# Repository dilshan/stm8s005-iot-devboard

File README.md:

# STM8S005C6T6 Ethernet development board

This is an Ethernet development board based on [STM8S005C6T6](https://www.st.com/resource/en/datasheet/stm8s005c6.pdf), designed specifically for IoT related applications. This development board consists of [ENC28J60](http://ww1.microchip.com/downloads/en/devicedoc/39662c.pdf), 10BASE-T stand-alone Ethernet controller, [CH340G](https://cdn.sparkfun.com/datasheets/Dev/Arduino/Other/CH340DS1.PDF), USB serial interface, 2 LED indicators, and passive buzzer unit.

The firmware framework for this development board has been developed using [SDCC](http://sdcc.sourceforge.net/). To enable IPv4 support, we convert the [EtherCard](https://github.com/njh/EtherCard) driver, which is available for the *Arduino* platform. The current version of this driver supports all other *EtherCard* functions except TCP support.

In the given design, the SPI terminals of the MCU are connected to the ENC28J60 Ethernet controller. All SPI terminals, such as *MISO* / *PC7*, *MOSI* / *PC6*, and *SCK* / *PC5*, are connected directly to the Ethernet controller. In addition, the *PC4* terminal of the MCU is used as ENC28J60, *CHIP-SELECT*. 

The CH340G USB serial interface is connected to the *UART2* terminals of the MCU. In STM8S005C6T6, the *UART2* is mapped to the *PD6* and *PD5* terminals of the MCU. The USB interface of this development board consists of the jack-sense feature. The jack-sense status can access from *PD7*.

The minor peripherals such as LED indicators and buzzer are connected to the *PORTD* of the MCU. The LED indicators are connected to terminals *PD0* and *PD1* and can be activated or deactivated via jumpers. The passive buzzer is connected to *PD4* and can run through the STM8 beep sound generator unit.

All peripherals of this development board are powered by a 3.3V supply. The recommended supply voltage for this development board is  5V to 9V.

In addition to the STM8S005C6T6, this development board supports the following STM8 series, LQFP48 packaged microcontrollers: [STM8S007C8T6](https://www.st.com/resource/en/datasheet/stm8s007c8.pdf), [STM8S207C8T6](https://www.st.com/resource/en/datasheet/stm8s207c8.pdf), and [STM8S105C6T6](https://www.st.com/resource/en/datasheet/stm8s105c6.pdf).

The schematic and PCB design of this project is released under the terms of [CERN-OHL-W Version 2.0](https://ohwr.org/cern_ohl_w_v2.pdf). The firmware framework is released under the terms of the [GNU GPL 2.0](https://github.com/dilshan/stm8s005-iot-devboard/blob/main/LICENSE) license.

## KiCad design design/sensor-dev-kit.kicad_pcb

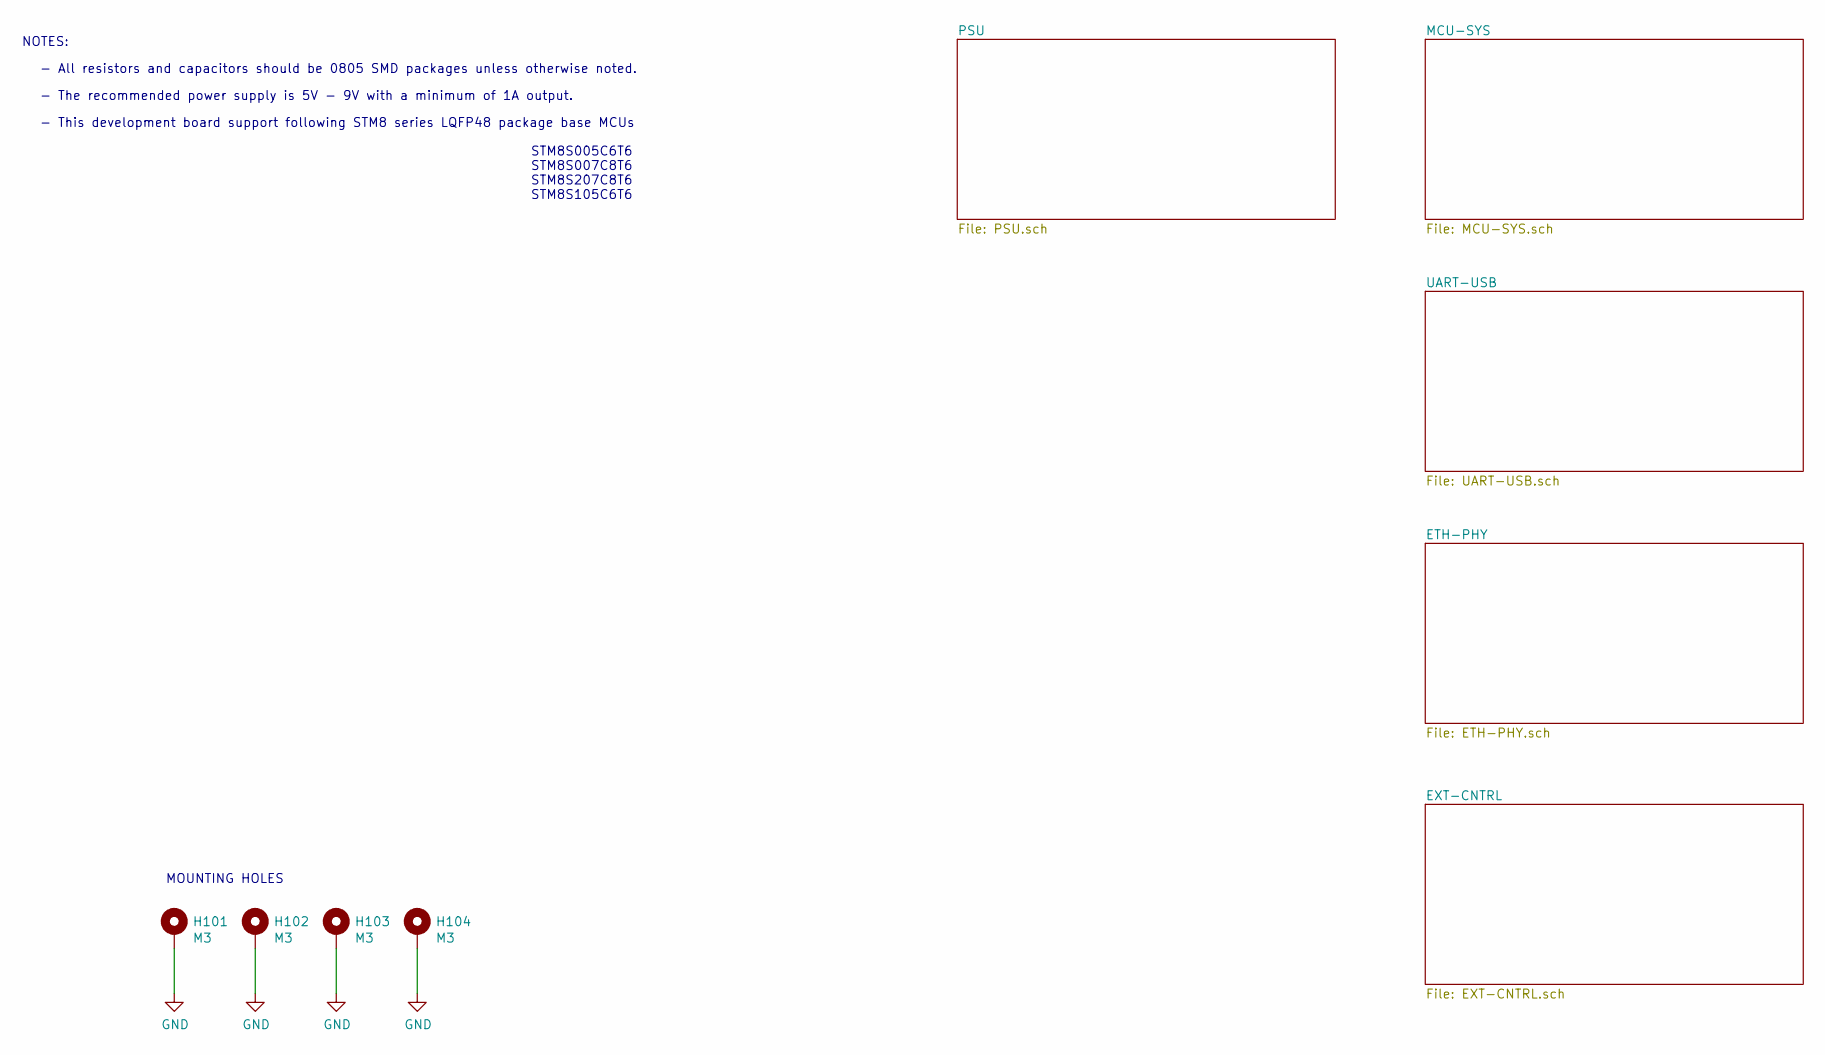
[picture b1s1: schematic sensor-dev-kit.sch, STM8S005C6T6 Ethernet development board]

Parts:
H101, H102, H103, H104: M3; MountingHole_3.2mm_M3_Pad_Via

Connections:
GND: H101.1, H102.1, H103.1, H104.1; also elsewhere on the board

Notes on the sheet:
NOTES:
- All resistors and capacitors should be 0805 SMD packages unless otherwise noted.
- The recommended power supply is 5V - 9V with a minimum of 1A output.
STM8S005C6T6 STM8S007C8T6 STM8S207C8T6 STM8S105C6T6
- This development board support following STM8 series LQFP48 package base MCUs
MOUNTING HOLES

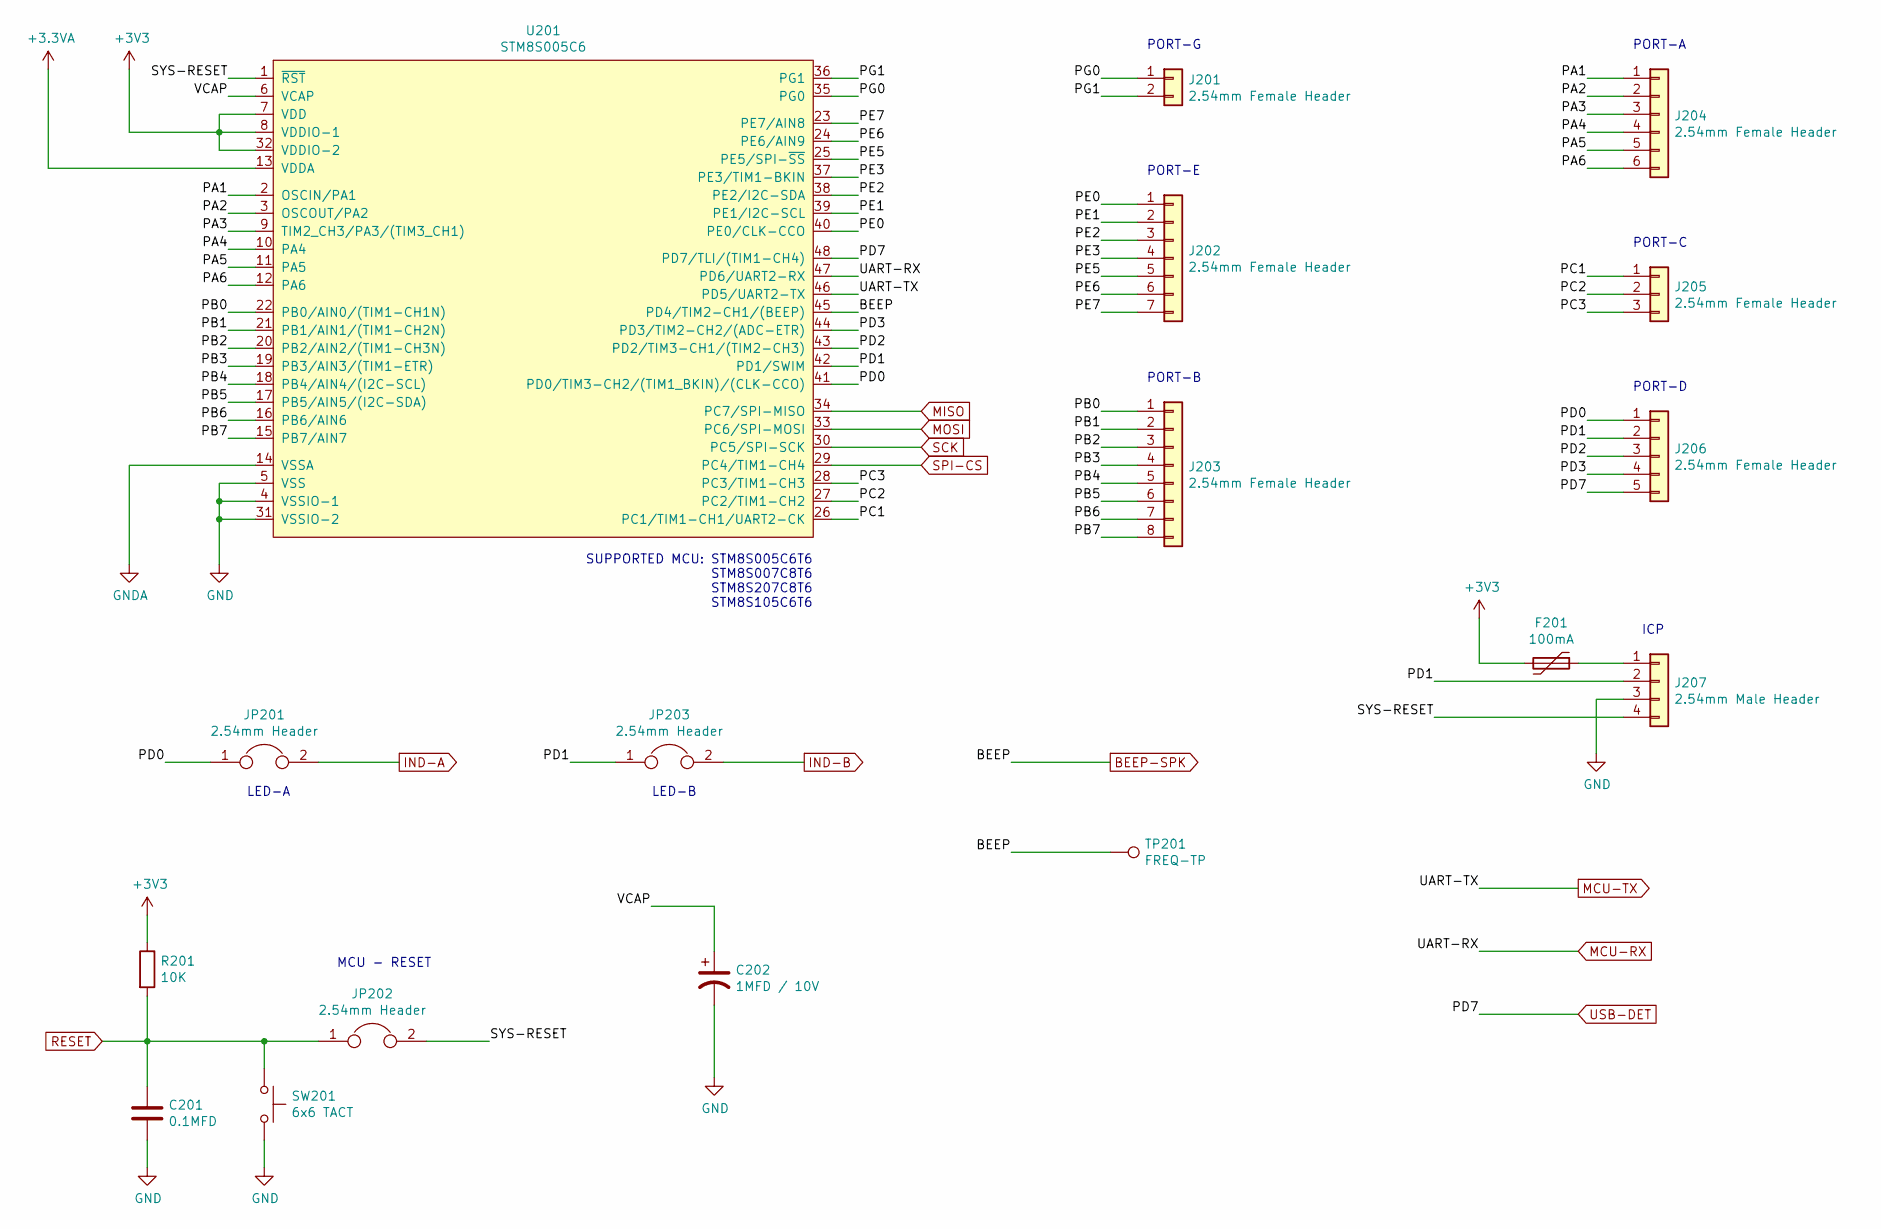
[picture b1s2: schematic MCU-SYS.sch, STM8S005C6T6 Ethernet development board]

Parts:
C201: 0.1MFD; C_0805_2012Metric_Pad1.18x1.45mm_HandSolder
C202: 1MFD / 10V; C_1206_3216Metric_Pad1.33x1.80mm_HandSolder
F201: 100mA; Fuse_1206_3216Metric_Pad1.42x1.75mm_HandSolder
J201: 2.54mm Female Header; PinHeader_1x02_P2.54mm_Vertical
J202: 2.54mm Female Header; PinHeader_1x07_P2.54mm_Vertical
J203: 2.54mm Female Header; PinHeader_1x08_P2.54mm_Vertical
J204: 2.54mm Female Header; PinHeader_1x06_P2.54mm_Vertical
J205: 2.54mm Female Header; PinHeader_1x03_P2.54mm_Vertical
J206: 2.54mm Female Header; PinHeader_1x05_P2.54mm_Vertical
J207: 2.54mm Male Header; PinHeader_1x04_P2.54mm_Vertical
JP201, JP202, JP203: 2.54mm Header; PinHeader_1x02_P2.54mm_Vertical
R201: 10K; R_0805_2012Metric_Pad1.20x1.40mm_HandSolder
SW201: 6x6 TACT; SW_PUSH_6mm
TP201: FREQ-TP; TestPoint_Pad_D1.0mm
U201: STM8S005C6; LQFP-48_7x7mm_P0.5mm

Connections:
+3.3VA: U201.13 (VDDA); also elsewhere on the board
+3V3: F201.2, R201.1, U201.7 (VDD), U201.8 (VDDIO-1), U201.32 (VDDIO-2); also elsewhere on the board
/MCU-SYS/PA1: J204.1, U201.2 (OSCIN/PA1)
/MCU-SYS/PA2: J204.2, U201.3 (OSCOUT/PA2)
/MCU-SYS/PA3: J204.3, U201.9 (TIM2_CH3/PA3/(TIM3_CH1))
/MCU-SYS/PA4: J204.4, U201.10 (PA4)
/MCU-SYS/PA5: J204.5, U201.11 (PA5)
/MCU-SYS/PA6: J204.6, U201.12 (PA6)
/MCU-SYS/PB0: J203.1, U201.22 (PB0/AIN0/(TIM1-CH1N))
/MCU-SYS/PB1: J203.2, U201.21 (PB1/AIN1/(TIM1-CH2N))
/MCU-SYS/PB2: J203.3, U201.20 (PB2/AIN2/(TIM1-CH3N))
/MCU-SYS/PB3: J203.4, U201.19 (PB3/AIN3/(TIM1-ETR))
/MCU-SYS/PB4: J203.5, U201.18 (PB4/AIN4/(I2C-SCL))
/MCU-SYS/PB5: J203.6, U201.17 (PB5/AIN5/(I2C-SDA))
/MCU-SYS/PB6: J203.7, U201.16 (PB6/AIN6)
/MCU-SYS/PB7: J203.8, U201.15 (PB7/AIN7)
/MCU-SYS/PC1: J205.1, U201.26 (PC1/TIM1-CH1/UART2-CK)
/MCU-SYS/PC2: J205.2, U201.27 (PC2/TIM1-CH2)
/MCU-SYS/PC3: J205.3, U201.28 (PC3/TIM1-CH3)
/MCU-SYS/PD0: J206.1, JP201.1, U201.41 (PD0/TIM3-CH2/(TIM1_BKIN)/(CLK-CCO))
/MCU-SYS/PD1: J206.2, J207.2, JP203.1, U201.42 (PD1/SWIM)
/MCU-SYS/PD2: J206.3, U201.43 (PD2/TIM3-CH1/(TIM2-CH3))
/MCU-SYS/PD3: J206.4, U201.44 (PD3/TIM2-CH2/(ADC-ETR))
/MCU-SYS/PE0: J202.1, U201.40 (PE0/CLK-CCO)
/MCU-SYS/PE1: J202.2, U201.39 (PE1/I2C-SCL)
/MCU-SYS/PE2: J202.3, U201.38 (PE2/I2C-SDA)
/MCU-SYS/PE3: J202.4, U201.37 (PE3/TIM1-BKIN)
/MCU-SYS/PE5: J202.5, U201.25 (PE5/SPI-~SS)
/MCU-SYS/PE6: J202.6, U201.24 (PE6/AIN9)
/MCU-SYS/PE7: J202.7, U201.23 (PE7/AIN8)
/MCU-SYS/PG0: J201.1, U201.35 (PG0)
/MCU-SYS/PG1: J201.2, U201.36 (PG1)
/MCU-SYS/SYS-RESET: J207.4, JP202.2, U201.1 (~RST)
/MCU-SYS/VCAP: C202.1, U201.6 (VCAP)
BEEP-SPK: TP201.1, U201.45 (PD4/TIM2-CH1/(BEEP)); also elsewhere on the board
GND: C201.2, C202.2, J207.3, SW201.2, U201.4 (VSSIO-1), U201.5 (VSS), U201.31 (VSSIO-2); also elsewhere on the board
GNDA: U201.14 (VSSA); also elsewhere on the board
IND-A: JP201.2; also elsewhere on the board
IND-B: JP203.2; also elsewhere on the board
MCU-RX: U201.47 (PD6/UART2-RX); also elsewhere on the board
MCU-TX: U201.46 (PD5/UART2-TX); also elsewhere on the board
MISO: U201.34 (PC7/SPI-MISO); also elsewhere on the board
MOSI: U201.33 (PC6/SPI-MOSI); also elsewhere on the board
unnamed: F201.1, J207.1
RESET: C201.1, JP202.1, R201.2, SW201.1; also elsewhere on the board
SCK: U201.30 (PC5/SPI-SCK); also elsewhere on the board
SPI-CS: U201.29 (PC4/TIM1-CH4); also elsewhere on the board
USB-DET: J206.5, U201.48 (PD7/TLI/(TIM1-CH4)); also elsewhere on the board

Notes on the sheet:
PORT-G
PORT-E
PORT-B
PORT-A
PORT-C
PORT-D
ICP
LED-A
LED-B
MCU - RESET
SUPPORTED MCU: STM8S005C6T6 STM8S007C8T6 STM8S207C8T6 STM8S105C6T6

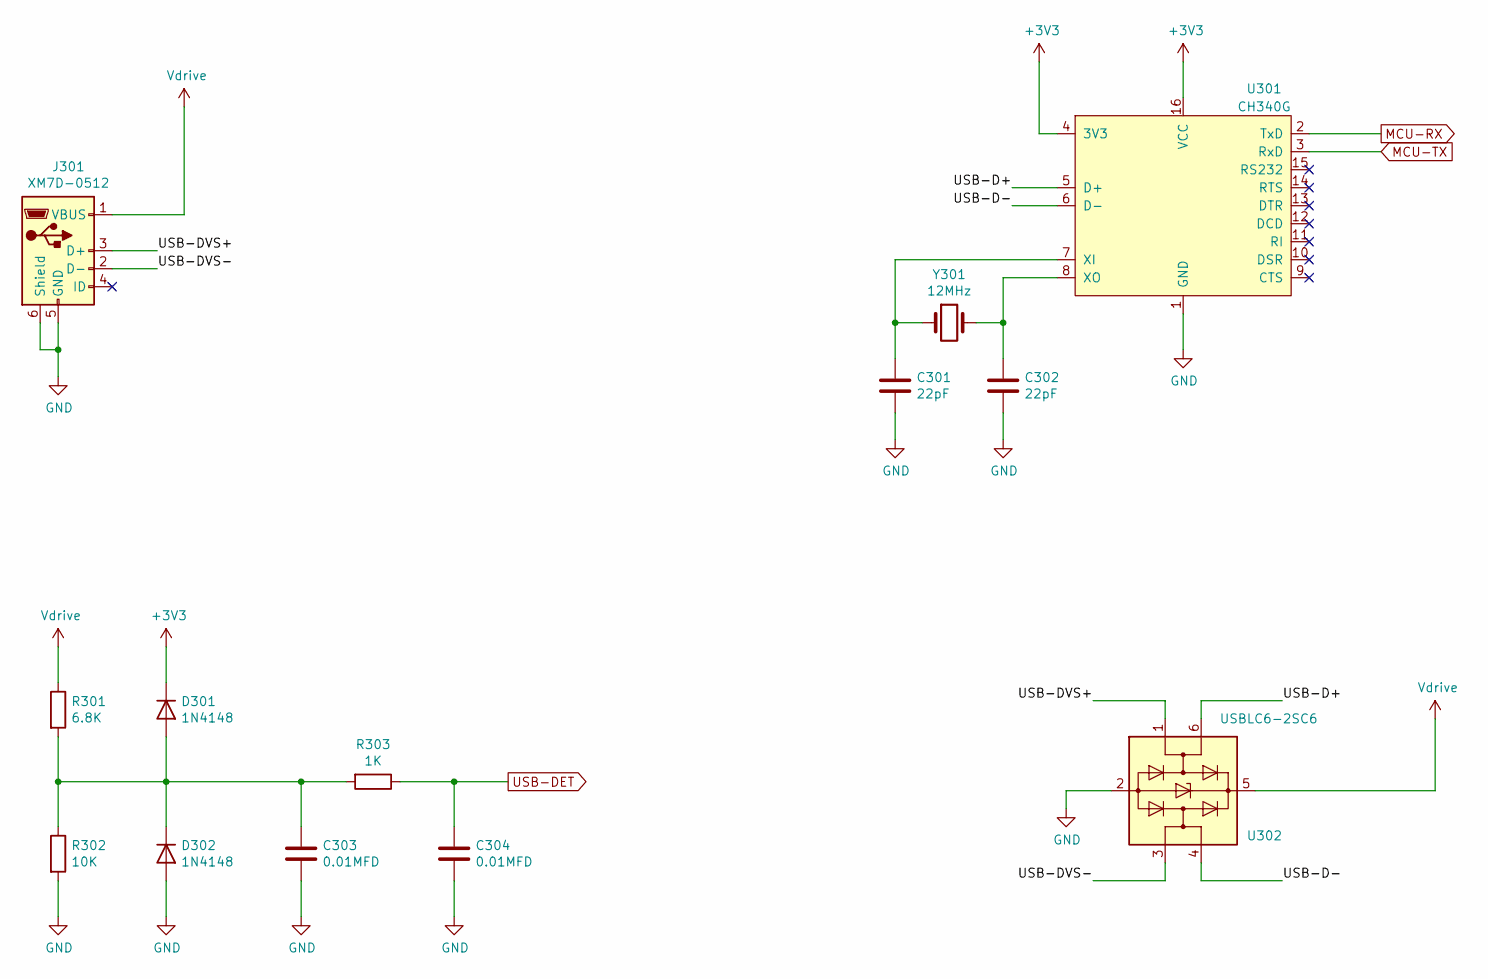
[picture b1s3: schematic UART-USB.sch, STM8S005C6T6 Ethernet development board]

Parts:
C301, C302: 22pF; C_0805_2012Metric_Pad1.18x1.45mm_HandSolder
C303, C304: 0.01MFD; C_0805_2012Metric_Pad1.18x1.45mm_HandSolder
D301, D302: 1N4148; D_MiniMELF_Handsoldering
J301: XM7D-0512; OMRON_XM7D-0512
R301: 6.8K; R_0805_2012Metric_Pad1.20x1.40mm_HandSolder
R302: 10K; R_0805_2012Metric_Pad1.20x1.40mm_HandSolder
R303: 1K; R_0805_2012Metric_Pad1.20x1.40mm_HandSolder
U301: CH340G; SOP-16_3.9x9.9mm_P1.27mm
U302: USBLC6-2SC6; SOT-23-6
Y301: 12MHz; Crystal_HC49-U_Vertical

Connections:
+3V3: D301.1 (K), U301.4 (3V3), U301.16 (VCC); also elsewhere on the board
/UART-USB/USB-D+: U301.5 (D+), U302.6 (I/O1)
/UART-USB/USB-D-: U301.6 (D-), U302.4 (I/O2)
/UART-USB/USB-DVS+: J301.3 (D+), U302.1 (I/O1)
/UART-USB/USB-DVS-: J301.2 (D-), U302.3 (I/O2)
GND: C301.2, C302.2, C303.2, C304.2, D302.2 (A), J301.5 (GND), J301.6 (Shield), R302.2, U301.1 (GND), U302.2 (GND); also elsewhere on the board
MCU-RX: U301.2 (TxD); also elsewhere on the board
MCU-TX: U301.3 (RxD); also elsewhere on the board
unnamed: C301.1, U301.7 (XI), Y301.1
unnamed: C302.1, U301.8 (XO), Y301.2
unnamed: C303.1, D301.2 (A), D302.1 (K), R301.2, R302.1, R303.2
USB-DET: C304.1, R303.1; also elsewhere on the board
Vdrive: J301.1 (VBUS), R301.1, U302.5 (VBUS)

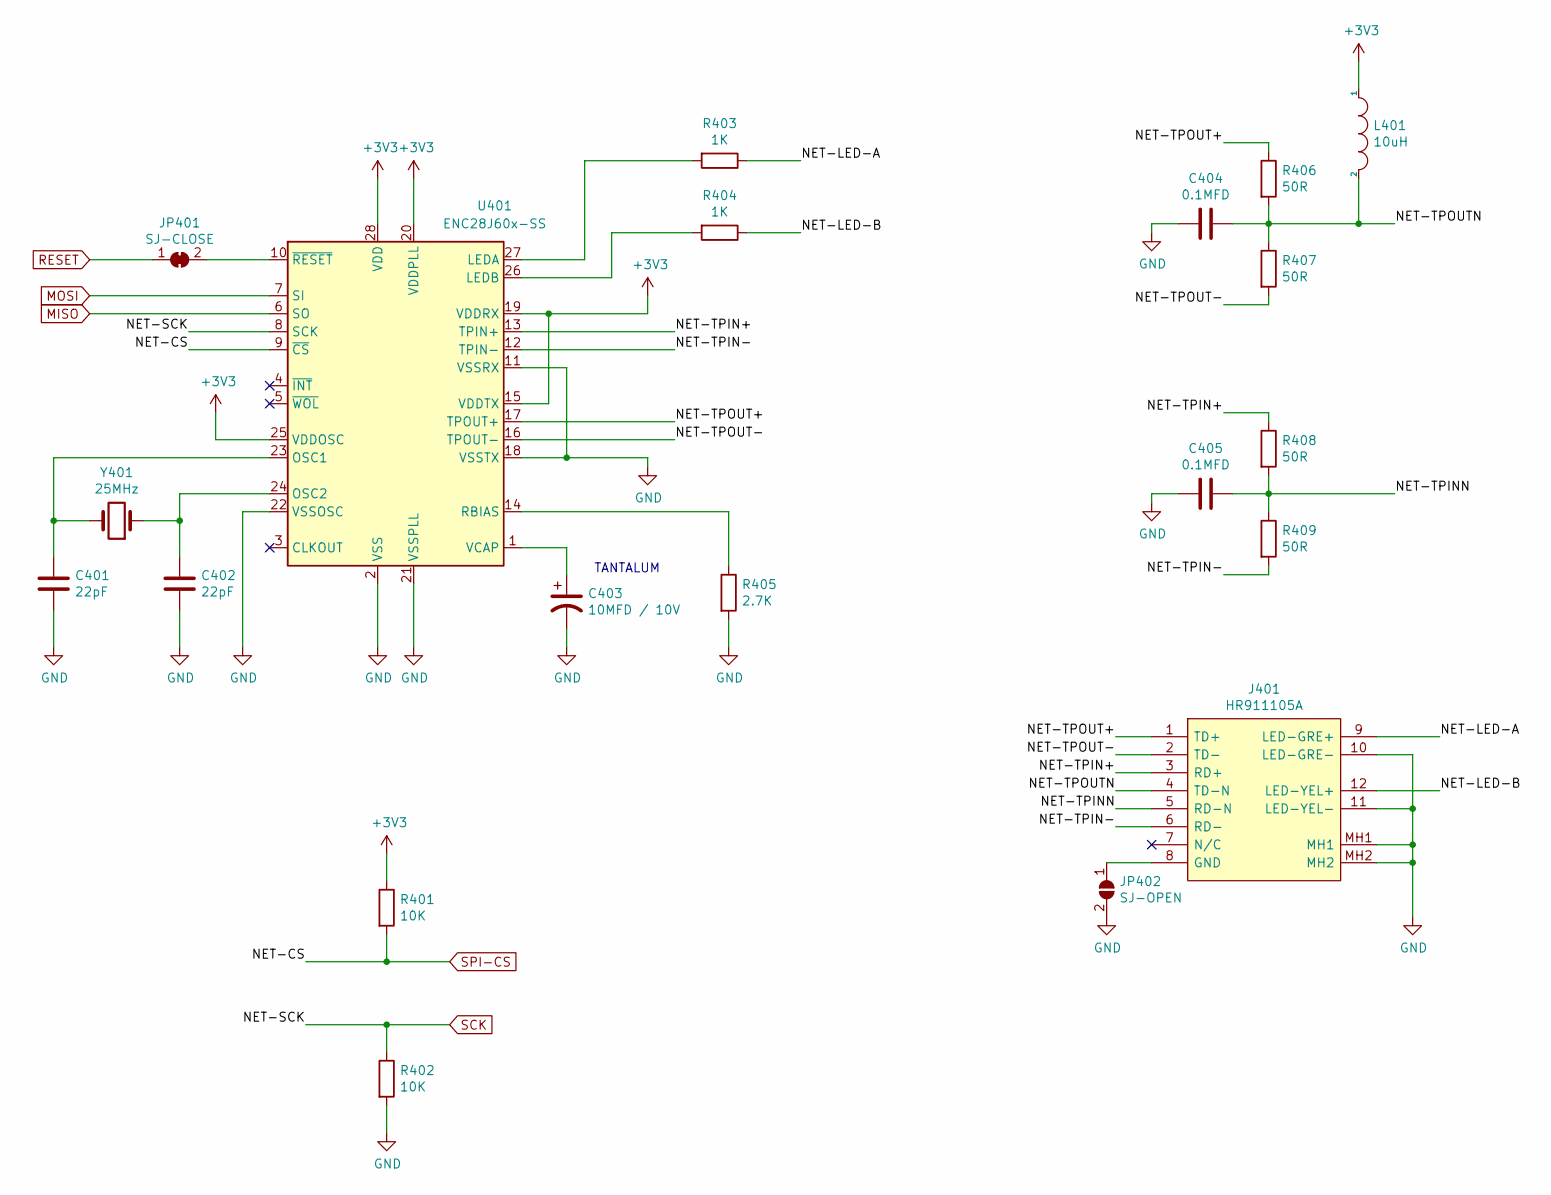
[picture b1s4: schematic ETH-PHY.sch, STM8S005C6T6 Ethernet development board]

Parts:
C401, C402: 22pF; C_0805_2012Metric_Pad1.18x1.45mm_HandSolder
C403: 10MFD / 10V; C_1206_3216Metric_Pad1.33x1.80mm_HandSolder
C404, C405: 0.1MFD; C_0805_2012Metric_Pad1.18x1.45mm_HandSolder
J401: HR911105A; Manufacturer_Part_Number HR911105A
JP401: SJ-CLOSE; SolderJumper-2_P1.3mm_Bridged2Bar_RoundedPad1.0x1.5mm
JP402: SJ-OPEN; SolderJumper-2_P1.3mm_Open_RoundedPad1.0x1.5mm
L401: 10uH; L_0805_2012Metric_Pad1.15x1.40mm_HandSolder
R401, R402: 10K; R_0805_2012Metric_Pad1.20x1.40mm_HandSolder
R403, R404: 1K; R_0805_2012Metric_Pad1.20x1.40mm_HandSolder
R405: 2.7K; R_0805_2012Metric_Pad1.20x1.40mm_HandSolder
R406, R407, R408, R409: 50R; R_0805_2012Metric_Pad1.20x1.40mm_HandSolder
U401: ENC28J60x-SS; SSOP-28_5.3x10.2mm_P0.65mm
Y401: 25MHz; Crystal_HC49-U_Vertical

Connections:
+3V3: L401.1, R401.1, U401.15 (VDDTX), U401.19 (VDDRX), U401.20 (VDDPLL), U401.25 (VDDOSC), U401.28 (VDD); also elsewhere on the board
/ETH-PHY/NET-LED-A: J401.9 (LED-GRE+), R403.1
/ETH-PHY/NET-LED-B: J401.12 (LED-YEL+), R404.1
/ETH-PHY/NET-TPIN+: J401.3 (RD+), R408.1, U401.13 (TPIN+)
/ETH-PHY/NET-TPIN-: J401.6 (RD-), R409.2, U401.12 (TPIN-)
/ETH-PHY/NET-TPINN: C405.1, J401.5 (RD-N), R408.2, R409.1
/ETH-PHY/NET-TPOUT+: J401.1 (TD+), R406.1, U401.17 (TPOUT+)
/ETH-PHY/NET-TPOUT-: J401.2 (TD-), R407.2, U401.16 (TPOUT-)
/ETH-PHY/NET-TPOUTN: C404.1, J401.4 (TD-N), L401.2, R406.2, R407.1
GND: C401.2, C402.2, C403.2, C404.2, C405.2, J401.10 (LED-GRE-), J401.11 (LED-YEL-), J401.MH1, J401.MH2, JP402.2 (B), R402.2, R405.2, U401.2 (VSS), U401.11 (VSSRX), U401.18 (VSSTX), U401.21 (VSSPLL), U401.22 (VSSOSC); also elsewhere on the board
MISO: U401.6 (SO); also elsewhere on the board
MOSI: U401.7 (SI); also elsewhere on the board
unnamed: C401.1, U401.23 (OSC1), Y401.2
unnamed: C402.1, U401.24 (OSC2), Y401.1
unnamed: C403.1, U401.1 (VCAP)
unnamed: J401.8 (GND), JP402.1 (A)
unnamed: JP401.2 (B), U401.10 (~RESET)
unnamed: R403.2, U401.27 (LEDA)
unnamed: R404.2, U401.26 (LEDB)
unnamed: R405.1, U401.14 (RBIAS)
RESET: JP401.1 (A); also elsewhere on the board
SCK: R402.1, U401.8 (SCK); also elsewhere on the board
SPI-CS: R401.2, U401.9 (~CS); also elsewhere on the board

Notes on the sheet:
TANTALUM

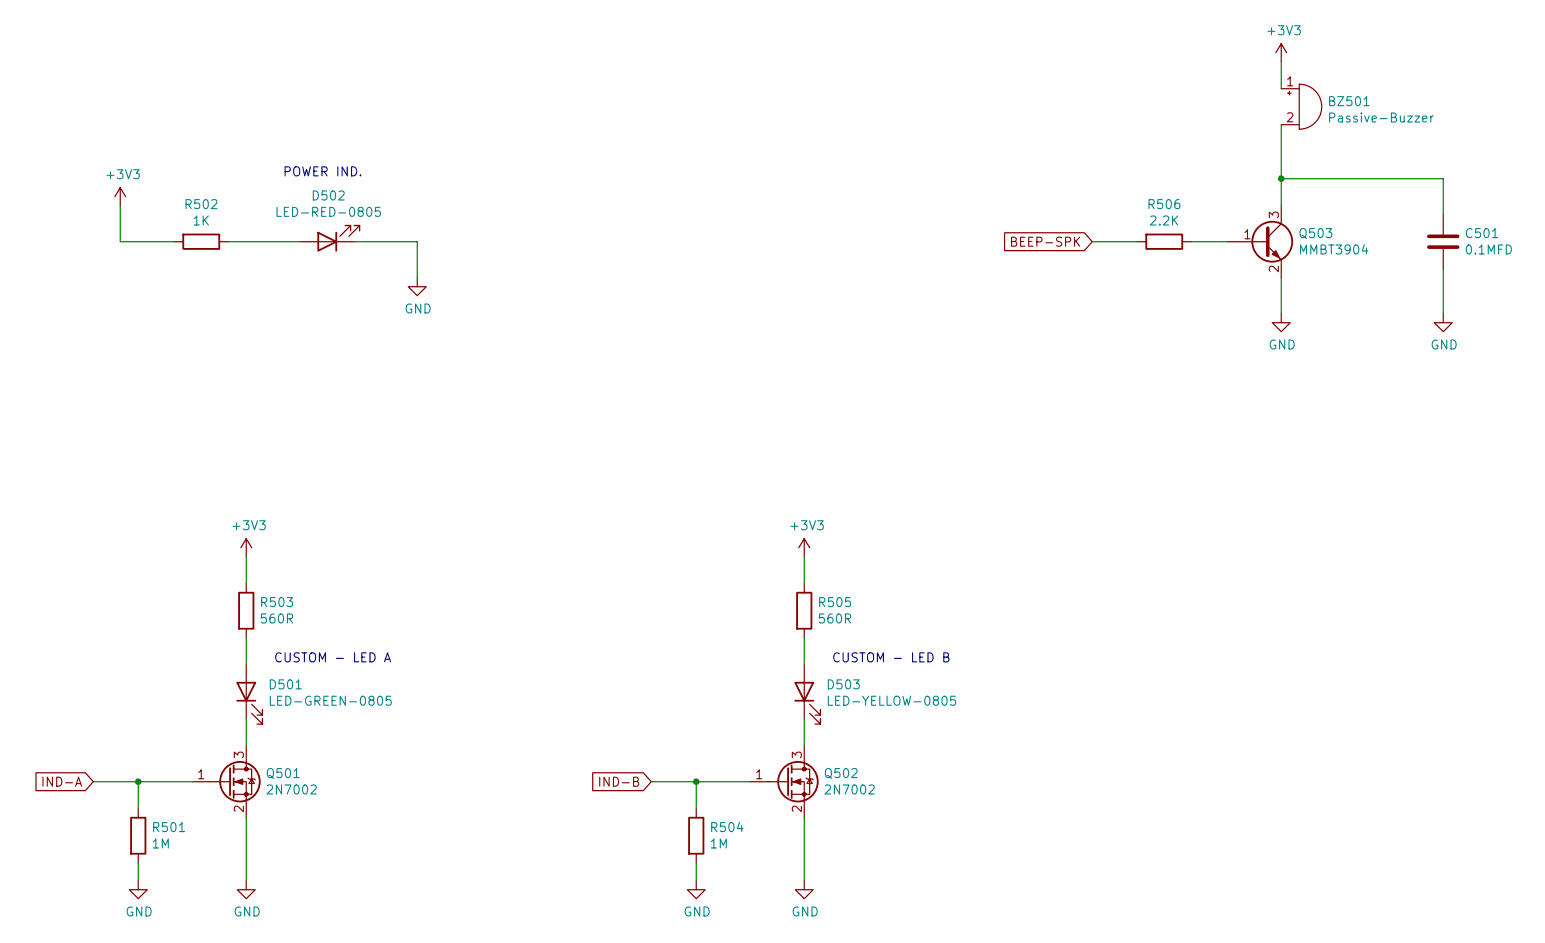
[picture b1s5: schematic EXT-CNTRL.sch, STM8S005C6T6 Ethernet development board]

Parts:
BZ501: Passive-Buzzer; Buzzer_12x9.5RM7.6
C501: 0.1MFD; C_0805_2012Metric_Pad1.18x1.45mm_HandSolder
D501: LED-GREEN-0805; LED_0805_2012Metric_Pad1.15x1.40mm_HandSolder
D502: LED-RED-0805; LED_0805_2012Metric_Pad1.15x1.40mm_HandSolder
D503: LED-YELLOW-0805; LED_0805_2012Metric_Pad1.15x1.40mm_HandSolder
Q501, Q502: 2N7002; SOT-23
Q503: MMBT3904; SOT-23
R501, R504: 1M; R_0805_2012Metric_Pad1.20x1.40mm_HandSolder
R502: 1K; R_0805_2012Metric_Pad1.20x1.40mm_HandSolder
R503, R505: 560R; R_0805_2012Metric_Pad1.20x1.40mm_HandSolder
R506: 2.2K; R_0805_2012Metric_Pad1.20x1.40mm_HandSolder

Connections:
+3V3: BZ501.1 (-), R502.2, R503.1, R505.1; also elsewhere on the board
BEEP-SPK: R506.2; also elsewhere on the board
GND: C501.2, D502.1 (K), Q501.2 (S), Q502.2 (S), Q503.2 (E), R501.2, R504.2; also elsewhere on the board
IND-A: Q501.1 (G), R501.1; also elsewhere on the board
IND-B: Q502.1 (G), R504.1; also elsewhere on the board
unnamed: BZ501.2 (+), C501.1, Q503.3 (C)
unnamed: D501.1 (K), Q501.3 (D)
unnamed: D501.2 (A), R503.2
unnamed: D502.2 (A), R502.1
unnamed: D503.1 (K), Q502.3 (D)
unnamed: D503.2 (A), R505.2
unnamed: Q503.1 (B), R506.1

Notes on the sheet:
CUSTOM - LED B
CUSTOM - LED A
POWER IND.

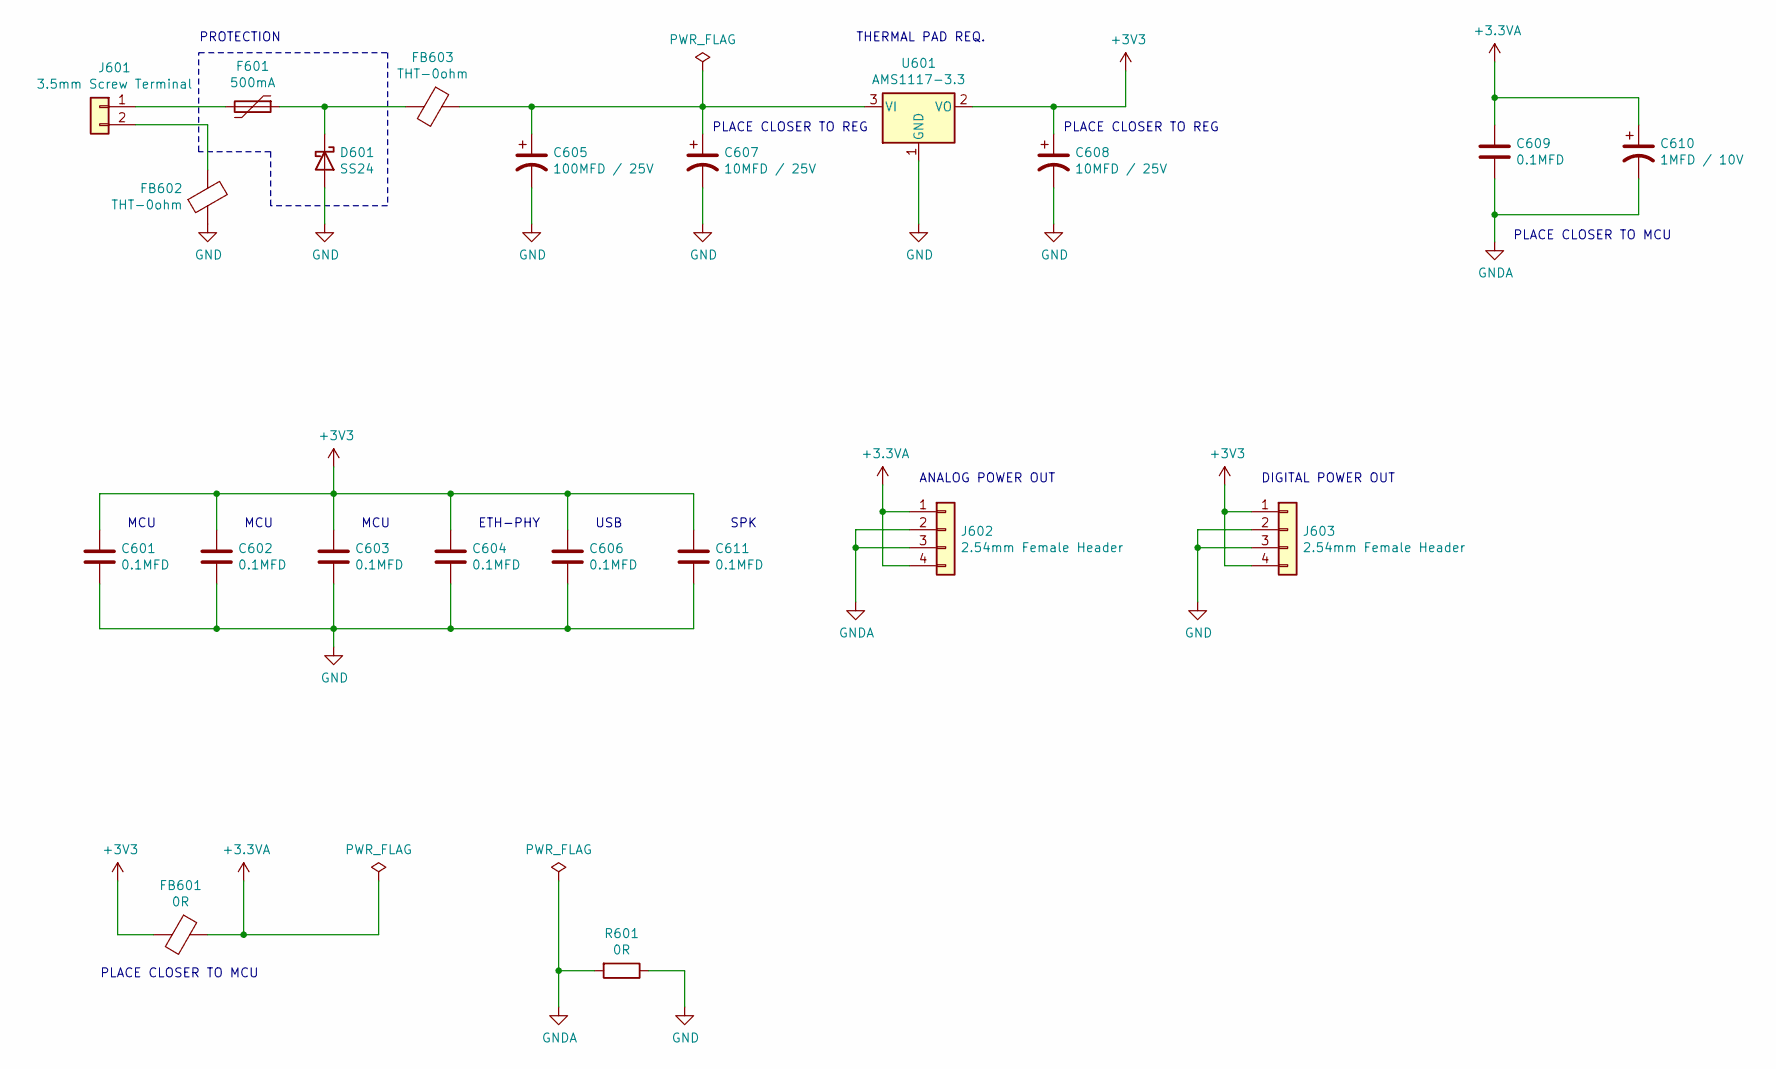
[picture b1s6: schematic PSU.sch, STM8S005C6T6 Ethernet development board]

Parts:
C601, C602, C603, C604, C606, C609, C611: 0.1MFD; C_0805_2012Metric_Pad1.18x1.45mm_HandSolder
C605: 100MFD / 25V; CP_Radial_D6.3mm_P2.50mm
C607, C608: 10MFD / 25V; CP_Radial_D5.0mm_P2.00mm
C610: 1MFD / 10V; C_0805_2012Metric_Pad1.18x1.45mm_HandSolder
D601: SS24; D_SMB_Handsoldering
F601: 500mA; Fuse_2816_7142Metric_Pad3.20x4.45mm_HandSolder
FB601: 0R; L_Axial_L6.6mm_D2.7mm_P10.16mm_Horizontal_Vishay_IM-2
FB602, FB603: THT-0ohm; L_Axial_L6.6mm_D2.7mm_P10.16mm_Horizontal_Vishay_IM-2
J601: 3.5mm Screw Terminal; PhoenixContact_MCV_1,5_2-G-3.5_1x02_P3.50mm_Vertical
J602, J603: 2.54mm Female Header; PinHeader_1x04_P2.54mm_Vertical
R601: 0R; R_0805_2012Metric_Pad1.20x1.40mm_HandSolder
U601: AMS1117-3.3; SOT-223-3_TabPin2

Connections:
+3.3VA: C609.1, C610.1, FB601.1, J602.1, J602.4; also elsewhere on the board
+3V3: C601.1, C602.1, C603.1, C604.1, C606.1, C608.1, C611.1, FB601.2, J603.1, J603.4, U601.2 (VO); also elsewhere on the board
GND: C601.2, C602.2, C603.2, C604.2, C605.2, C606.2, C607.2, C608.2, C611.2, D601.2 (A), FB602.1, J603.2, J603.3, R601.1, U601.1 (GND); also elsewhere on the board
GNDA: C609.2, C610.2, J602.2, J602.3, R601.2; also elsewhere on the board
unnamed: C605.1, C607.1, FB603.1, U601.3 (VI)
unnamed: D601.1 (K), F601.1, FB603.2
unnamed: F601.2, J601.1
unnamed: FB602.2, J601.2

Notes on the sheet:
PLACE CLOSER TO REG
PROTECTION
PLACE CLOSER TO MCU
ANALOG POWER OUT
DIGITAL POWER OUT
THERMAL PAD REQ.
MCU
ETH-PHY
USB
SPK

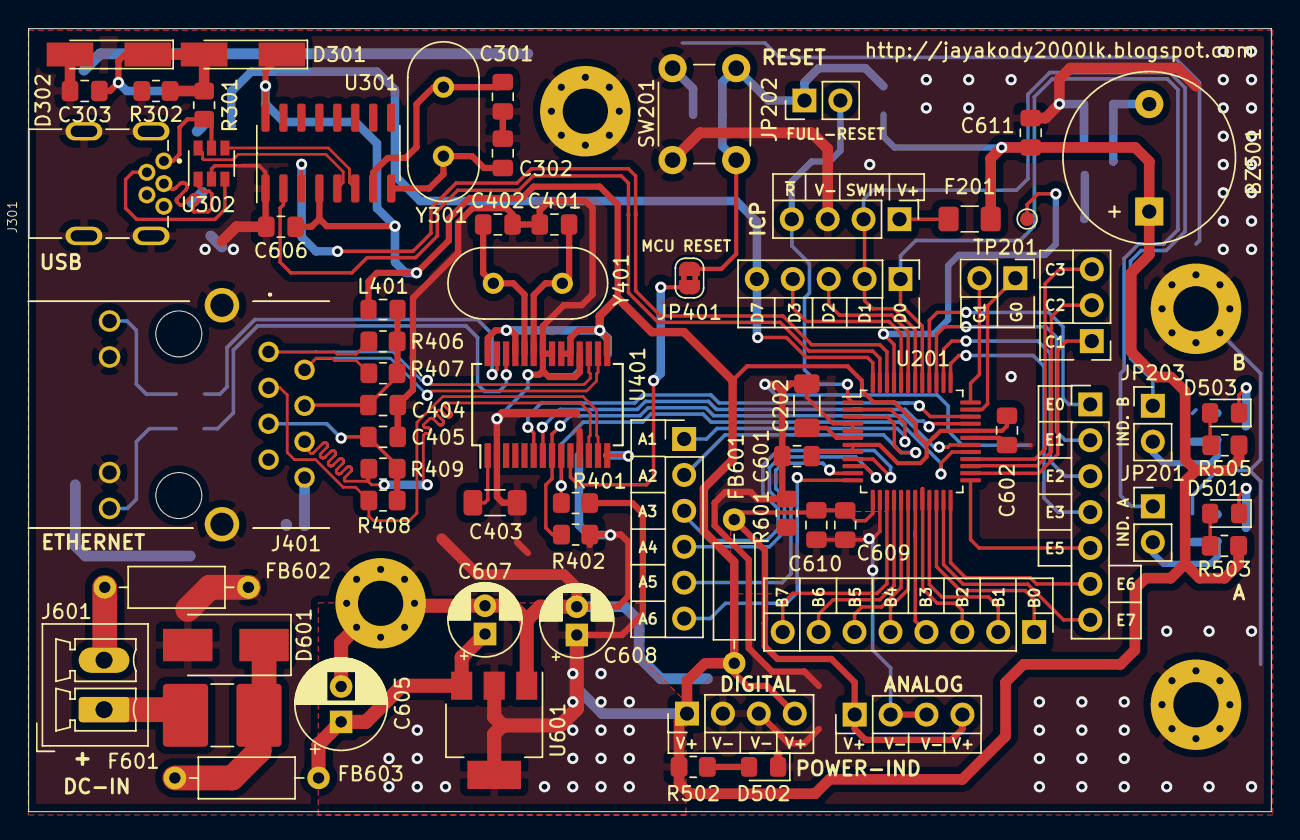
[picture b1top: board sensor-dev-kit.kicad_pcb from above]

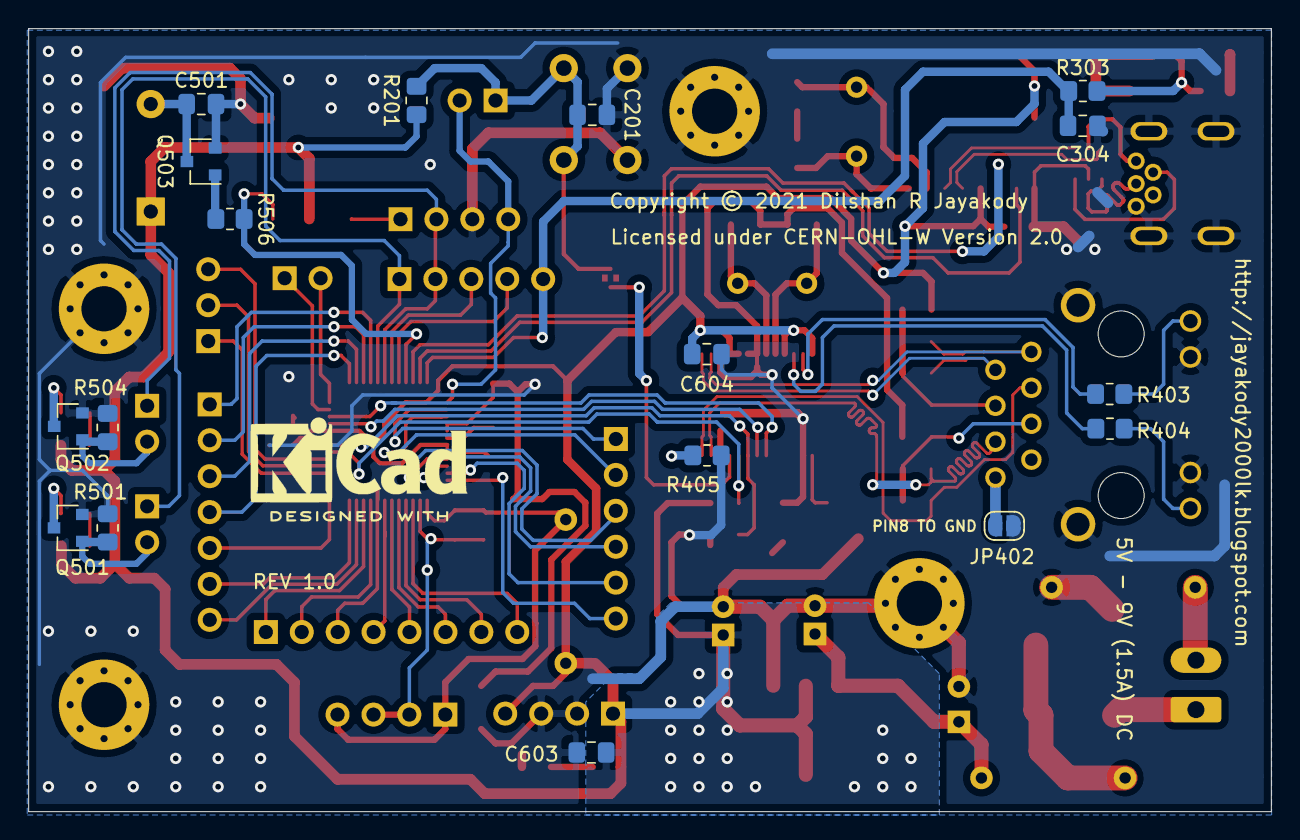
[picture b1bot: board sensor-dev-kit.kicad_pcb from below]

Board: 2 copper layers, 87.9 x 55.4 mm, 89 parts (17 on the bottom side), 83 nets.

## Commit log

2021-11-14 Add initial version of development board design files.
2021-11-15 Add initial version of STM8S firmware files.
2021-11-15 Fix source code formating issues in ENC28J60 driver.
2021-11-15 Add image of the IoT development board.
2021-11-15 Initial version of readme.md file.
2021-11-15 Create action workflow to build the source with SDCC on Ubuntu image.
2021-11-15 Add BOM files in PDF and LibreOffice Calc formats.
2021-11-15 Fix minor formatting issues in readme.md file.

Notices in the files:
design/ETH-PHY.sch:
License under CERN-OHL-W Version 2.0
design/sensor-dev-kit.kicad_pcb:
Copyright © 2021 Dilshan R Jayakody
Licensed under CERN-OHL-W Version 2.0
